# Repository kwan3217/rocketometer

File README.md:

# rocketometer
Rocketometer -- inertial, pressure, and maybe GPS sensors for measuring a sounding rocket

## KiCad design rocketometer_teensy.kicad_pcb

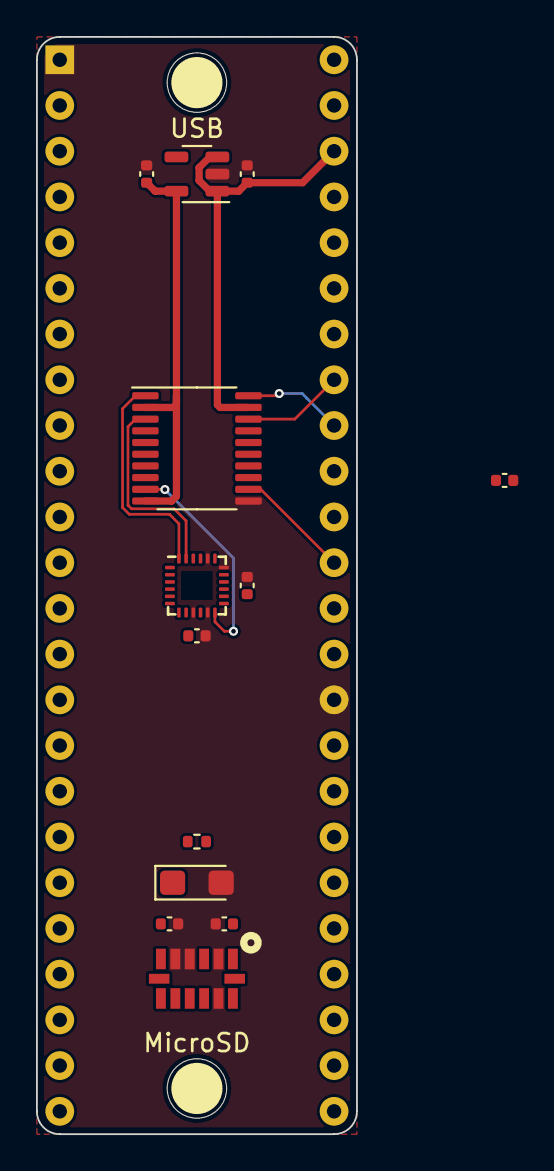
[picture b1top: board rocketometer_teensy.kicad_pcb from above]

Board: 2 copper layers, 17.8 x 61.0 mm, 16 parts (0 on the bottom side), 11 nets.

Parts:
C208, C210, C213, C401, C405: 100nF; C_0402_1005Metric
C301, C305: 1uF; C_0402_1005Metric
C406: 10uF; CP_EIA-3216-18_Kemet-A
J101: Teensy4.1; DIP-48_W15.24mm
J102, J103: STANDOFF; STANDOFF_NONPLATED
R406: 100; R_0402_1005Metric
U101: TXS0108EPW; TSSOP-20_4.4x6.5mm_P0.65mm
U201: ICM-20948; InvenSense_QFN-24_3x3mm_P0.4mm
U301: TCR2EF 1.8V; SOT-23-5
U401: ADXL375

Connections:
+1V8: C208.1, C213.1, C305.1, U101.2 (VCCA), U101.10 (OE), U201.8 (VDDIO), U201.13 (VDD), U201.22 (~CS), U301.5 (OUT)
+3V3: C301.1, C401.1, J101.15 (+3V3), J101.46 (+3V3), R406.1, U101.19 (VCCB), U301.1 (IN), U301.3 (EN), U401.1 (VDDIO), U401.7 (~CS)
/HiAcc/VS: C405.1, C406.1, R406.2, U401.6 (VS)
/IMU_DRDY_1V8: U101.9 (A8), U201.12 (INT1)
/IMU_DRDY_3V3: J101.37 (~D15), U101.12 (B8)
/SCL_1V8: U101.3 (A2), U201.23 (SCL/SCLK)
/SCL_3V3: J101.41 (~D19), U101.18 (B2), U401.14 (SCL)
/SDA_1V8: U101.1 (A1), U201.24 (SDA/SDI)
/SDA_3V3: J101.40 (~D18), U101.20 (B1), U401.13 (SDA)
GND: C208.2, C210.2, C213.2, C301.2, C305.2, C401.2, C405.2, C406.2, J101.1 (GND), J101.34 (GND), U101.11 (GND), U201.9 (SDO/AD0), U201.11 (FSYNC), U201.18 (GND), U201.20 (GND), U301.2 (GND), U401.2 (GND), U401.4 (GND), U401.5 (GND), U401.12 (ALT_ADDR)
unnamed: C210.1, U201.10 (REGOUT)

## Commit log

2022-12-13 Create LICENSE
2022-12-13 Added initial (empty) KiCad files
2022-12-13 Added kwan_kicad_lib as a submodule
2022-12-13 Moved ICM-20948 schematic to kwan_kicad_lib
2022-12-13 Trying to change merge behavior of submodule (no detached HEAD)
